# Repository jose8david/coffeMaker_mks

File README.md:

# ☕ Proyecto de domotización de la cafetera Dolce Gusto del Makespace

Este proyecto tiene como objetivo **domotizar una cafetera de cápsulas Nescafé Dolce Gusto de Krups**.  
En concreto, se pretende:

- 🔸 Automatizar el **tiempo de dispensación del café**.  
- 🔸 Automatizar el **encendido y apagado** cuando la máquina permanezca inactiva.

---

## Cómo hacerse un café

Para preparar un café, sigue estos pasos:

1. **Enciende la máquina** mediante el botón lateral derecho con las marcas `0/I`.  
   La posición `I` indica que la máquina está encendida.
2. **Coloca la cápsula** en su soporte y ciérralo correctamente.  
3. **Espera** a que el **LED verde** situado encima del soporte deje de parpadear y se mantenga fijo.  
4. **Pulsa una vez el botón amarillo**, situado junto al botón de encendido/apagado general (`0/I`).

---

## Funcionamiento de la domotización

Después de realizar las cuatro operaciones anteriores, la máquina **suministra agua caliente** a través de la cápsula durante **20 segundos**. ¡Tenemos café!

- Si se vuelve a pulsar el **botón amarillo** durante este proceso, la máquina **detiene inmediatamente** la dispensación de agua (modo de parada de emergencia).  
- Al volver a pulsarlo, **reanuda la operación** durante otros 20 segundos.

Además:

- Si transcurren **dos minutos sin pulsar el botón amarillo**, la máquina **desconecta el calderín**, aunque **no se apaga por completo**. Por ello, **es importante dejar el botón lateral en la posición `0`** cuando no se vaya a utilizar.

---

## Explicación sencilla del circuito

Al conectar la máquina a la corriente y colocar el botón de encendido en la posición `I`, se genera un voltaje de 5 V.  
Este voltaje pasa por un diodo (para evitar inversiones de polaridad) y alimenta los siguientes componentes:

-  **ESP8266**
-  **Dos relés**, que controlan:
  - El **calderín** (pin D3)
  - La **bomba de agua** (pin D4)
- **Un botón**, conectado con una resistencia de **10 kΩ** en configuración *pull-up* al pin D2.
- **Un sensor NTC**, conectado como divisor de tensión con una resistencia de **100 kΩ** al pin A0.  
  El divisor se alimenta con **3,3 V** procedentes del propio ESP8266.

---

### Proceso de funcionamiento

1. Al encender la máquina, el **calderín comienza a calentarse** hasta alcanzar una temperatura aproximada de **60 °C a 70 °C**.  
   (Se supone que el circuito original incluye alguna protección, como un **fusible térmico**, para cortar la corriente al calderín en caso de sobrecalentamiento).

2. Mientras tanto, el ESP8266 permanece a la espera de que se pulse el botón amarillo (una vez la cápsula esté colocada y el LED verde se mantenga fijo).

3. Al pulsar el botón:
   - El ESP8266 lee la temperatura mediante el NTC, que está en contacto con el calderín.  
   - Si la temperatura igual o supera los 60 °C, se activa el relé que controla la bomba de agua.

4. El relé de la bomba se mantiene cerrado durante 20 segundos, tiempo durante el cual la máquina dispensa agua caliente a través de la cápsula.

---

## Componentes principales

| Componente | Función | Pin del ESP8266 |
|-------------|----------|----------------|
| Relé 1 | Control del calderín | D3~0 |
| Relé 2 | Control de la bomba de agua | D4~2 |
| Botón amarillo | Activación de la dispensación | D2~4 |
| Sensor NTC | Lectura de temperatura del calderín | A0~A0 |

---

## 📜 ANÍMATE A SEGUIR CON EL PROYECTO

- 💡 Pon el funcionamiento las tiras LED que cubren la carcasa de la cafetera. ¿Qué tal si indicasen el tiempo de inactividad? ¿ o la temperatura?
- 💡 Conecta el ESP8266 a internet y avanza con la domotización

---

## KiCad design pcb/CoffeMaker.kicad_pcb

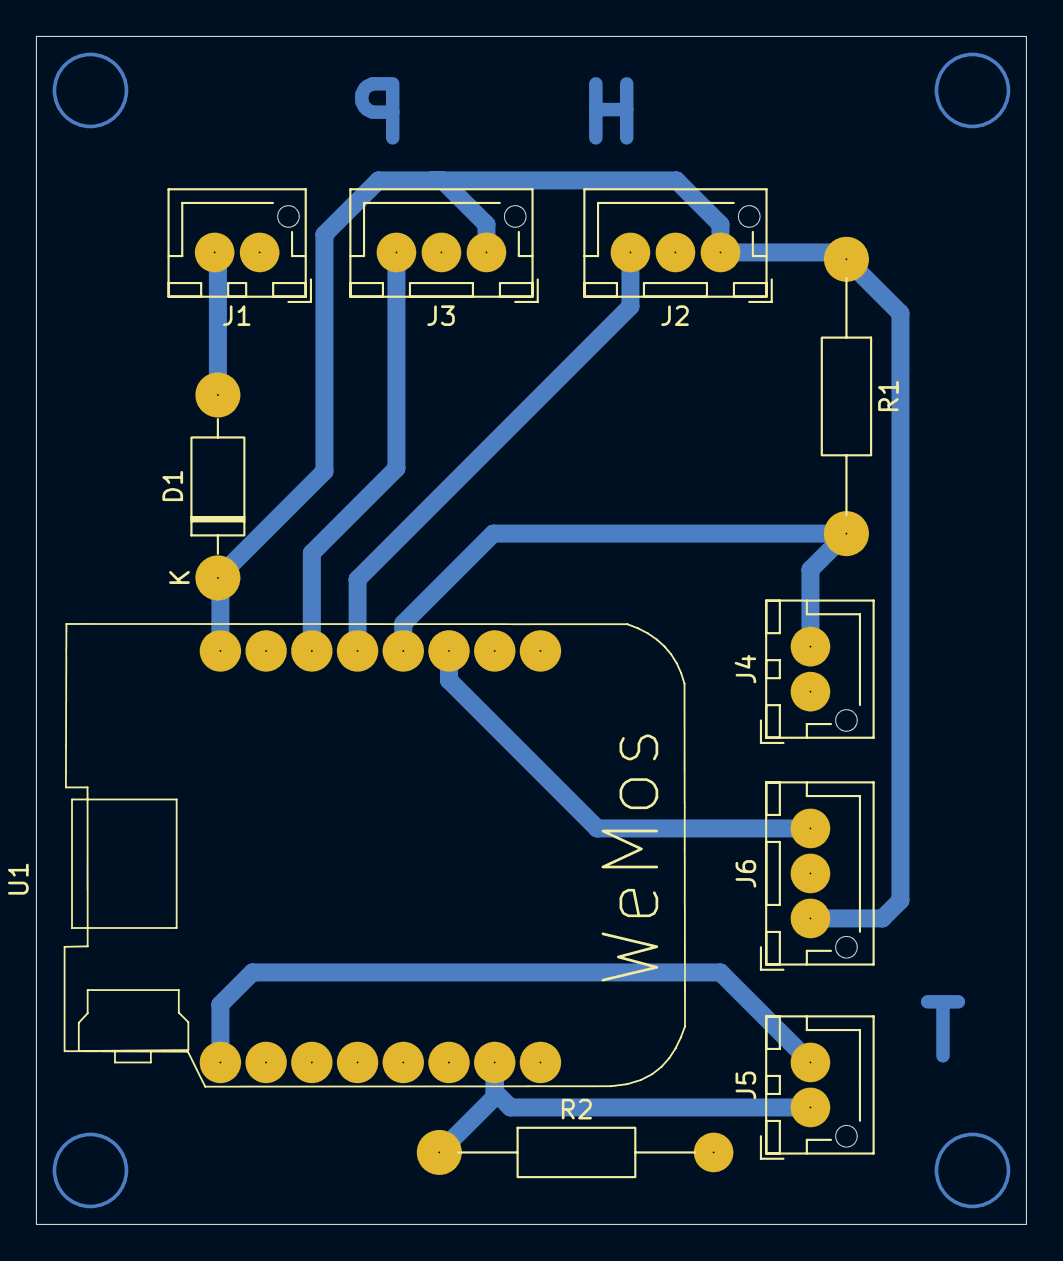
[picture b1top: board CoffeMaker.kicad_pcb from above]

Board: 2 copper layers, 55.0 x 66.0 mm, 10 parts (0 on the bottom side), 9 nets.

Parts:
D1: SB130; D_DO-41_SOD81_P10.16mm_Horizontal
J1: POWER; JST_XH_B2B-XH-AM_1x02_P2.50mm_Vertical
J2: HEATER_RELAY; JST_XH_B3B-XH-AM_1x03_P2.50mm_Vertical
J3: PUMP_RELAY; JST_XH_B3B-XH-AM_1x03_P2.50mm_Vertical
J4: POWER_BUTTON; JST_XH_B2B-XH-AM_1x02_P2.50mm_Vertical
J5: TEMP_SENSOR; JST_XH_B2B-XH-AM_1x02_P2.50mm_Vertical
J6: LED_STRIP; JST_XH_B3B-XH-AM_1x03_P2.50mm_Vertical
R1: 10K; R_Axial_DIN0207_L6.3mm_D2.5mm_P15.24mm_Horizontal
R2: 100K; R_Axial_DIN0207_L6.3mm_D2.5mm_P15.24mm_Horizontal
U1: Wemos mini D1 ESP8266; D1_mini_board

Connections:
+3V3: J5.2, U1.16 (3.3V)
+5V: D1.1 (K), J2.1, J3.1, J6.1, R1.1, U1.e (5V)
BTN: J4.2, R1.2, U1.5 (D2)
GND: J1.1, J2.2, J3.2, J4.1, J6.2, R2.2, U1.2 (GND)
HEATER: J2.3, U1.4 (D3)
LED: J6.3, U1.6 (D1)
unnamed: D1.2 (A), J1.2
PUMP: J3.3, U1.3 (D4)
TMP: J5.1, R2.1, U1.10 (A0)

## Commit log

2025-10-07 Archivos del código y de la PCB
2025-10-07 Explicación del funcionamiento
2025-10-07 Documentación mínima que explica el funcionamiento de la cafetera
